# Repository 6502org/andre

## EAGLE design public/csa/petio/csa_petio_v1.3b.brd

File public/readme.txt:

TODO: 

- move unused img sources to ../imgsrc

- make build scripts for sprites, javascript (see below)

create sprite:

- menu items are scaled to 41% to be included in sprite

- cbm/hw/sw/icap icons are not scaled 

minify javascript:

- yui-compressor --nomunge myscripts.js > myscripts-min.js

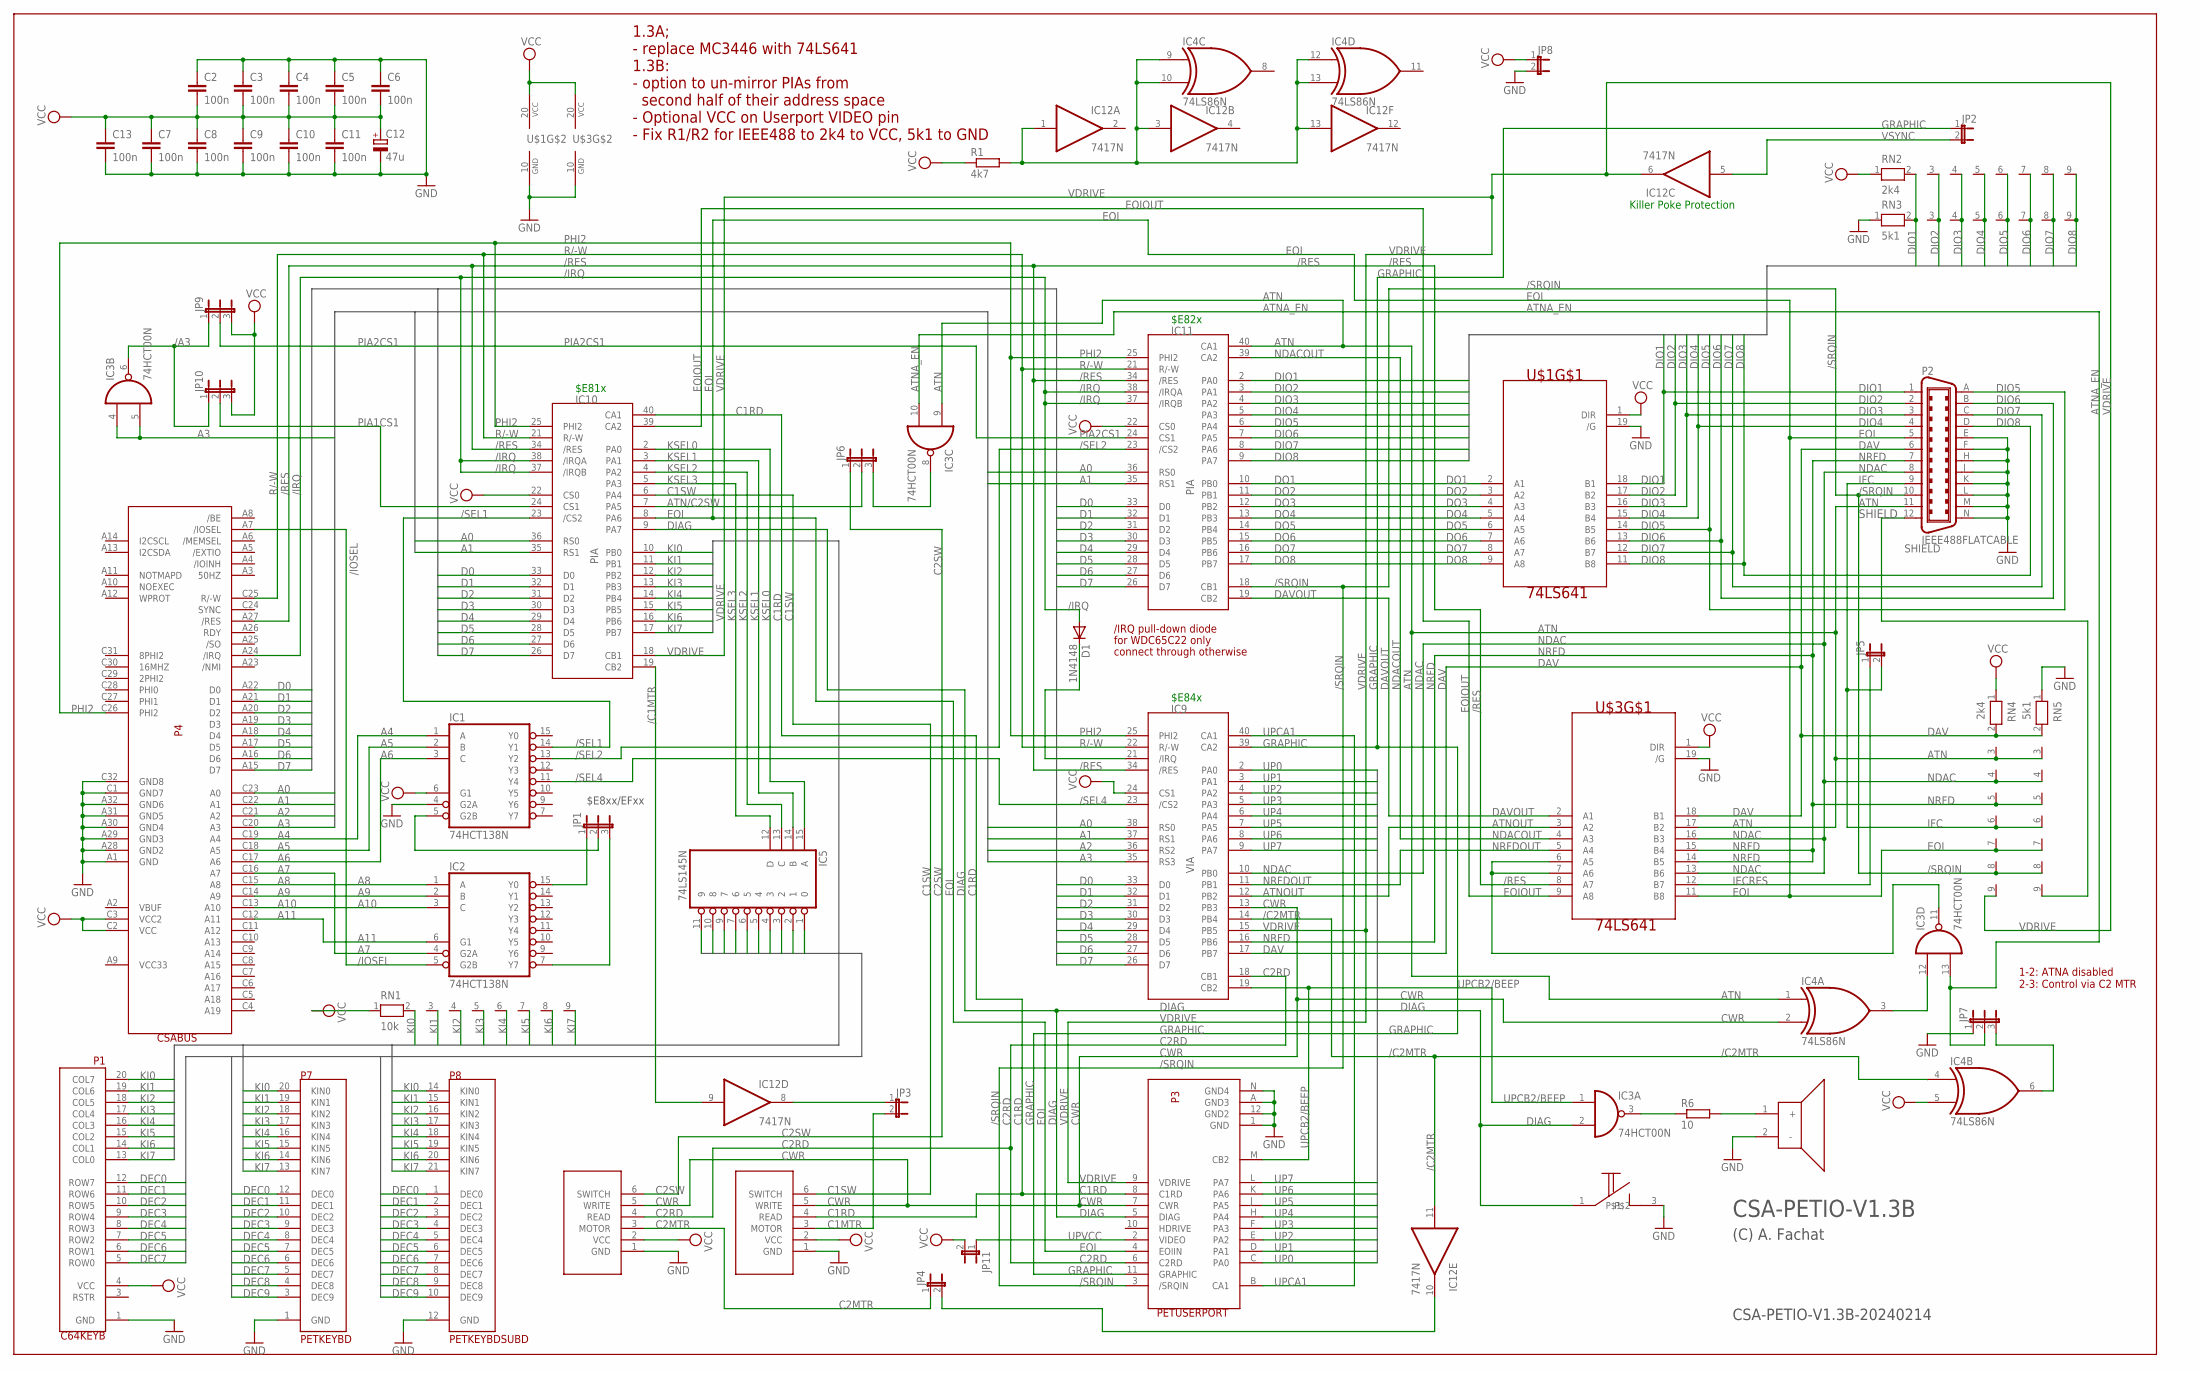
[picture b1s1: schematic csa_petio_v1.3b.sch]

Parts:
BEEP1: PIEZOBEEPERPIEZO; PIEZOBEEPER
C2, C3, C4, C5, C6, C7, C8, C9, C10, C11, C13: 100n; C025-025X050
C12: 47u; E2,5-6
D1: 1N4148; D-5
IC1, IC2: 74HCT138N; DIL16
IC3: 74HCT00N; DIL14
IC4: 74LS86N; DIL14
IC5: 74LS145N; DIL16
IC9: VIA; DIL40
IC10, IC11: PIA; DIL40
IC12: 7417N; DIL14
JP1, JP6, JP7, JP9, JP10: JP2E; JP2
JP2, JP3, JP4, JP5, JP8, JP11: JP1E; JP1
P1: C64KEYB
P2: IEEE488FLATCABLE; FLAT24
P3: PETUSERPORT; FLAT24
P4: CSABUS
P5, P6: CBMTAPE; JP6
P7: PETKEYBD; C64KEYB
P8: PETKEYBDSUBD; SUBD25F
R1: 4k7; 0207/10
R6: 10; 0207/10
RN1: 10k; RN-9
RN2, RN4: 2k4; RN-9
RN3, RN5: 5k1; RN-9
U$1, U$3: 74LS641; DIL20
U$2: TASTER

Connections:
//C2MTR: IC4.6 (O), JP7.3
/A3: IC3.6 (O), JP9.1, JP10.1
/C1MTR: IC10.19 (CB2), IC12.9 (I)
/C2MTR: IC4.4 (I0), IC9.14 (PB4), IC12.11 (I)
/IOSEL: IC2.5 (G2B), P4.A7 (/IOSEL)
/IRQ: D1.A, IC10.37 (/IRQB), IC10.38 (/IRQA), IC11.37 (/IRQB), IC11.38 (/IRQA), P4.A24 (/IRQ)
/RES: IC9.34 (/RES), IC10.34 (/RES), IC11.34 (/RES), P4.A27 (/RES), U$3.8 (A7)
/SEL1: IC1.14 (Y1), IC10.23 (/CS2)
/SEL2: IC1.13 (Y2), IC11.23 (/CS2)
/SEL4: IC1.11 (Y4), IC9.23 (/CS2)
/SRQIN: IC11.18 (CB1), P2.10, P3.3 (/SRQIN), RN4.8, RN5.8
A0: IC9.38 (RS0), IC10.36 (RS0), IC11.36 (RS0), P4.C23 (A0)
A1: IC9.37 (RS1), IC10.35 (RS1), IC11.35 (RS1), P4.C22 (A1)
A2: IC9.36 (RS2), P4.C21 (A2)
A3: IC3.4 (I0), IC3.5 (I1), IC9.35 (RS3), P4.C20 (A3)
A4: IC1.1 (A), P4.C19 (A4)
A5: IC1.2 (B), P4.C18 (A5)
A6: IC1.3 (C), P4.C17 (A6)
A7: IC2.4 (G2A), P4.C16 (A7)
A8: IC2.1 (A), P4.C15 (A8)
A9: IC2.2 (B), P4.C14 (A9)
A10: IC2.3 (C), P4.C13 (A10)
A11: IC2.6 (G1), P4.C12 (A11)
ATN: IC3.9 (I0), IC4.1 (I0), IC11.40 (CA1), P2.11, RN4.3, RN5.3, U$3.17 (B2)
ATN/C2SW: IC10.7 (PA5), JP6.2
ATNA_EN: IC3.10 (I1), IC3.13 (I1), JP7.2
ATNOUT: IC9.12 (PB2), U$3.3 (A2)
C1MTR: JP3.2, P5.3 (MOTOR)
C1RD: IC10.40 (CA1), P3.8 (C1RD), P5.4 (READ)
C1SW: IC10.6 (PA4), P5.6 (SWITCH)
C2MTR: JP4.1, P6.3 (MOTOR)
C2RD: IC9.18 (CB1), P3.6 (C2RD), P6.4 (READ)
C2SW: JP6.1, P6.6 (SWITCH)
CWR: IC4.2 (I1), IC9.13 (PB3), P3.7 (CWR), P5.5 (WRITE), P6.5 (WRITE)
D0: IC9.33 (D0), IC10.33 (D0), IC11.33 (D0), P4.A22 (D0)
D1: IC9.32 (D1), IC10.32 (D1), IC11.32 (D1), P4.A21 (D1)
D2: IC9.31 (D2), IC10.31 (D2), IC11.31 (D2), P4.A20 (D2)
D3: IC9.30 (D3), IC10.30 (D3), IC11.30 (D3), P4.A19 (D3)
D4: IC9.29 (D4), IC10.29 (D4), IC11.29 (D4), P4.A18 (D4)
D5: IC9.28 (D5), IC10.28 (D5), IC11.28 (D5), P4.A17 (D5)
D6: IC9.27 (D6), IC10.27 (D6), IC11.27 (D6), P4.A16 (D6)
D7: IC9.26 (D7), IC10.26 (D7), IC11.26 (D7), P4.A15 (D7)
DAV: IC9.17 (PB7), P2.6, RN4.2, RN5.2, U$3.18 (B1)
DAVOUT: IC11.19 (CB2), U$3.2 (A1)
DEC0: IC5.1 (0), P1.12 (ROW7), P7.12 (DEC0), P8.1 (DEC0)
DEC1: IC5.2 (1), P1.11 (ROW6), P7.11 (DEC1), P8.2 (DEC1)
DEC2: IC5.3 (2), P1.10 (ROW5), P7.10 (DEC2), P8.3 (DEC2)
DEC3: IC5.4 (3), P1.9 (ROW4), P7.9 (DEC3), P8.4 (DEC3)
DEC4: IC5.5 (4), P1.8 (ROW3), P7.8 (DEC4), P8.5 (DEC4)
DEC5: IC5.6 (5), P1.7 (ROW2), P7.7 (DEC5), P8.6 (DEC5)
DEC6: IC5.7 (6), P1.6 (ROW1), P7.6 (DEC6), P8.7 (DEC6)
DEC7: IC5.9 (7), P1.5 (ROW0), P7.5 (DEC7), P8.8 (DEC7)
DEC8: IC5.10 (8), P7.4 (DEC8), P8.9 (DEC8)
DEC9: IC5.11 (9), P7.3 (DEC9), P8.10 (DEC9)
DIAG: IC3.2 (I1), IC10.9 (PA7), P3.5 (DIAG), U$2.1
DIO1: IC11.2 (PA0), P2.1, RN2.2, RN3.2, U$1.18 (B1)
DIO2: IC11.3 (PA1), P2.2, RN2.3, RN3.3, U$1.17 (B2)
DIO3: IC11.4 (PA2), P2.3, RN2.4, RN3.4, U$1.16 (B3)
DIO4: IC11.5 (PA3), P2.4, RN2.5, RN3.5, U$1.15 (B4)
DIO5: IC11.6 (PA4), P2.A (13), RN2.6, RN3.6, U$1.14 (B5)
DIO6: IC11.7 (PA5), P2.B (14), RN2.7, RN3.7, U$1.13 (B6)
DIO7: IC11.8 (PA6), P2.C (15), RN2.8, RN3.8, U$1.12 (B7)
DIO8: IC11.9 (PA7), P2.D (16), RN2.9, RN3.9, U$1.11 (B8)
DO1: IC11.10 (PB0), U$1.2 (A1)
DO2: IC11.11 (PB1), U$1.3 (A2)
DO3: IC11.12 (PB2), U$1.4 (A3)
DO4: IC11.13 (PB3), U$1.5 (A4)
DO5: IC11.14 (PB4), U$1.6 (A5)
DO6: IC11.15 (PB5), U$1.7 (A6)
DO7: IC11.16 (PB6), U$1.8 (A7)
DO8: IC11.17 (PB7), U$1.9 (A8)
EOI: IC10.8 (PA6), P2.5, P3.4 (EOIIN), RN4.7, RN5.7, U$3.11 (B8)
EOIOUT: IC10.39 (CA2), U$3.9 (A8)
GND: BEEP1.2 (-), C2.1, C3.1, C4.1, C5.1, C6.1, C7.2, C8.2, C9.2, C10.2, C11.2, C12.-, C13.2, IC1.4 (G2A), IC1.8 (GND), IC2.8 (GND), IC3.7 (GND), IC4.7 (GND), IC5.8 (GND), IC9.1 (GND), IC10.1 (GND), IC11.1 (GND), IC12.7 (GND), JP7.1, JP8.2, P1.1 (GND), P2.E (17), P2.F (18), P2.H (19), P2.J (20), P2.K (21), P2.L (22), P2.M (23), P2.N (24), P3.1 (GND), P3.12 (GND2), P3.A (GND3), P3.N (GND4), P4.A1 (GND), P4.A28 (GND2), P4.A29 (GND3), P4.A30 (GND4), P4.A31 (GND5), P4.A32 (GND6), P4.C1 (GND7), P4.C32 (GND8), P5.1 (GND), P6.1 (GND), P7.1 (GND), P8.12 (GND), RN3.1, RN5.1, U$1.10 (GND), U$1.19 (/G), U$2.3, U$3.10 (GND), U$3.19 (/G)
GRAPHIC: IC9.39 (CA2), JP2.1, P3.11 (GRAPHIC)
IECRES: JP5.1, U$3.12 (B7)
IFC: JP5.2, P2.9, RN4.6, RN5.6
KI0: IC10.10 (PB0), P1.20 (COL7), P7.20 (KIN0), P8.14 (KIN0), RN1.2
KI1: IC10.11 (PB1), P1.19 (COL6), P7.19 (KIN1), P8.15 (KIN1), RN1.3
KI2: IC10.12 (PB2), P1.18 (COL5), P7.18 (KIN2), P8.16 (KIN2), RN1.4
KI3: IC10.13 (PB3), P1.17 (COL4), P7.17 (KIN3), P8.17 (KIN3), RN1.5
KI4: IC10.14 (PB4), P1.16 (COL3), P7.16 (KIN4), P8.18 (KIN4), RN1.6
KI5: IC10.15 (PB5), P1.15 (COL2), P7.15 (KIN5), P8.19 (KIN5), RN1.7
KI6: IC10.16 (PB6), P1.14 (COL1), P7.14 (KIN6), P8.20 (KIN6), RN1.8
KI7: IC10.17 (PB7), P1.13 (COL0), P7.13 (KIN7), P8.21 (KIN7), RN1.9
KSEL0: IC5.15 (A), IC10.2 (PA0)
KSEL1: IC5.14 (B), IC10.3 (PA1)
KSEL2: IC5.13 (C), IC10.4 (PA2)
KSEL3: IC5.12 (D), IC10.5 (PA3)
unnamed: IC3.12 (I0), IC4.3 (O)
unnamed: IC3.11 (O), U$3.6 (A5), U$3.7 (A6)
unnamed: IC3.3 (O), R6.1
unnamed: BEEP1.1 (+), R6.2
unnamed: D1.C, IC9.21 (/IRQ)
unnamed: IC3.8 (O), JP6.3
unnamed: IC12.8 (O), JP3.1
unnamed: IC12.10 (O), JP4.2
unnamed: IC1.5 (G2B), JP1.2
unnamed: IC2.15 (Y0), JP1.1
unnamed: IC2.7 (Y7), JP1.3
NDAC: IC9.10 (PB0), P2.8, RN4.4, RN5.4, U$3.13 (B6), U$3.16 (B3)
NDACOUT: IC11.39 (CA2), U$3.4 (A3)
NRFD: IC9.16 (PB6), P2.7, RN4.5, RN5.5, U$3.14 (B5), U$3.15 (B4)
NRFDOUT: IC9.11 (PB1), U$3.5 (A4)
OPENHIGH: IC4.9 (I0), IC4.10 (I1), IC4.12 (I0), IC4.13 (I1), IC12.1 (I), IC12.3 (I), IC12.13 (I), R1.2
PHI2: IC9.25 (PHI2), IC10.25 (PHI2), IC11.25 (PHI2), P4.C26 (PHI2)
PIA1CS1: IC10.24 (CS1), JP10.2
PIA2CS1: IC11.24 (CS1), JP9.2
R/-W: IC9.22 (R/-W), IC10.21 (R/-W), IC11.21 (R/-W), P4.C25 (R/-W)
SHIELD: P2.12, RN5.9
UP0: IC9.2 (PA0), P3.C (PA0)
UP1: IC9.3 (PA1), P3.D (PA1)
UP2: IC9.4 (PA2), P3.E (PA2)
UP3: IC9.5 (PA3), P3.F (PA3)
UP4: IC9.6 (PA4), P3.H (PA4)
UP5: IC9.7 (PA5), P3.J (PA5)
UP6: IC9.8 (PA6), P3.K (PA6)
UP7: IC9.9 (PA7), P3.L (PA7)
UPCA1: IC9.40 (CA1), P3.B (CA1)
UPCB2/BEEP: IC3.1 (I0), IC9.19 (CB2), P3.M (CB2)
UPVCC: JP11.1, P3.2 (VIDEO)
VCC: C2.2, C3.2, C4.2, C5.2, C6.2, C7.1, C8.1, C9.1, C10.1, C11.1, C12.+, C13.1, IC1.6 (G1), IC1.16 (VCC), IC2.16 (VCC), IC3.14 (VCC), IC4.5 (I1), IC4.14 (VCC), IC5.16 (VCC), IC9.20 (VCC), IC9.24 (CS1), IC10.20 (VCC), IC10.22 (CS0), IC11.20 (VCC), IC11.22 (CS0), IC12.14 (VCC), JP8.1, JP9.3, JP10.3, JP11.2, P1.4 (VCC), P4.C2 (VCC), P4.C3 (VCC2), P5.2 (VCC), P6.2 (VCC), R1.1, RN1.1, RN2.1, RN4.1, U$1.1 (DIR), U$1.20 (VCC), U$3.1 (DIR), U$3.20 (VCC)
VDRIVE: IC9.15 (PB5), IC10.18 (CB1), IC12.6 (O), P3.9 (VDRIVE), RN4.9
VSYNC: IC12.5 (I), JP2.2

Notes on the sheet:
$E8xx/EFxx
CSA-PETIO-V1.3B-20240214
CSA-PETIO-V1.3B
(C) A. Fachat
Killer Poke Protection
$E82x
$E84x
$E81x
/IRQ pull-down diode
for WDC65C22 only
connect through otherwise
1.3A; - replace MC3446 with 74LS641 1.3B: - option to un-mirror PIAs from second half of their address space - Optional VCC on Userport VIDEO pin - Fix R1/R2 for IEEE488 to 2k4 to VCC, 5k1 to GND
1-2: ATNA disabled 2-3: Control via C2 MTR

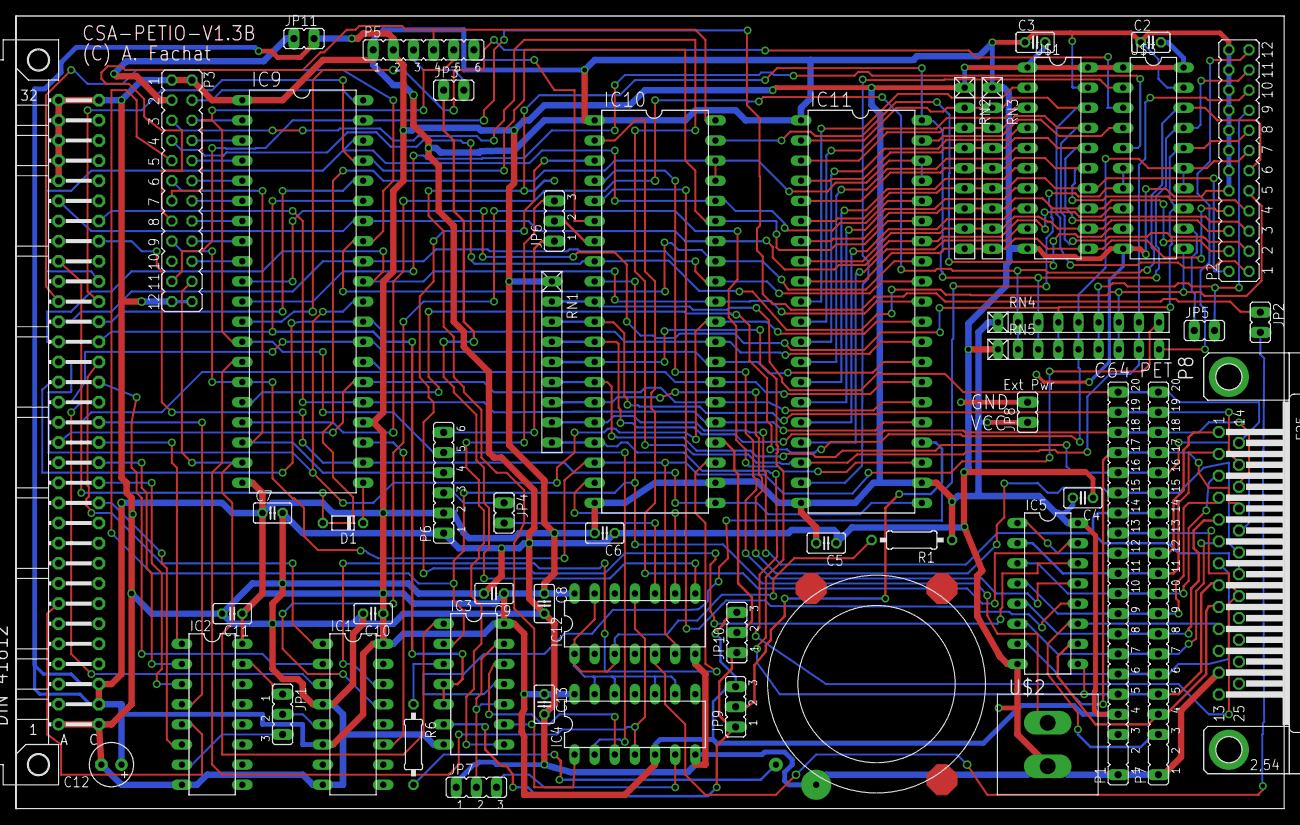
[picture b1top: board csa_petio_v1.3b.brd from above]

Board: 2 copper layers, 160.0 x 100.0 mm, 52 parts (0 on the bottom side), 124 nets.

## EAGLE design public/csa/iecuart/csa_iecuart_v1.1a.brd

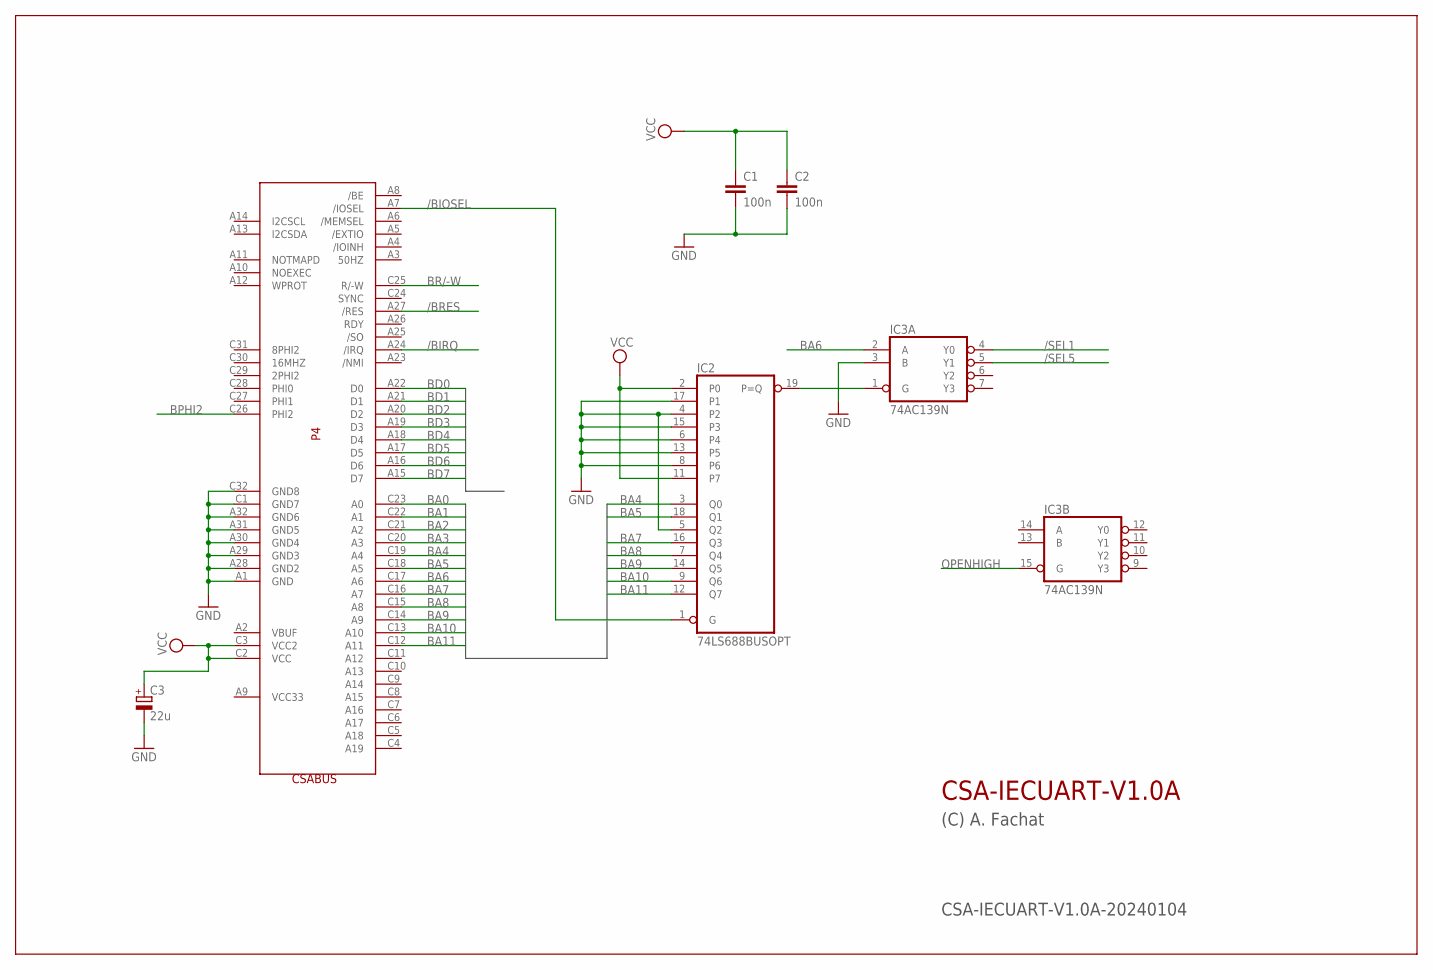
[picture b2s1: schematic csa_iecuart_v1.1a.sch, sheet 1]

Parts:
C1, C2: 100n; C025-024X044
C3: 22u; E2,5-7
IC2: 74LS688BUSOPT; DIL20
IC3: 74AC139N; DIL16
P4: CSABUS

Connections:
/BIOSEL: IC2.1 (G), P4.A7 (/IOSEL)
/BIRQ: P4.A24 (/IRQ); also elsewhere on the board
/BRES: P4.A27 (/RES); also elsewhere on the board
/SEL1: IC3.4 (Y0); also elsewhere on the board
/SEL5: IC3.5 (Y1); also elsewhere on the board
BA0: P4.C23 (A0); also elsewhere on the board
BA1: P4.C22 (A1); also elsewhere on the board
BA2: P4.C21 (A2); also elsewhere on the board
BA3: P4.C20 (A3); also elsewhere on the board
BA4: IC2.3 (Q0), P4.C19 (A4)
BA5: IC2.18 (Q1), P4.C18 (A5)
BA6: IC3.2 (A), P4.C17 (A6)
BA7: IC2.16 (Q3), P4.C16 (A7)
BA8: IC2.7 (Q4), P4.C15 (A8)
BA9: IC2.14 (Q5), P4.C14 (A9)
BA10: IC2.9 (Q6), P4.C13 (A10)
BA11: IC2.12 (Q7), P4.C12 (A11)
BD0: P4.A22 (D0); also elsewhere on the board
BD1: P4.A21 (D1); also elsewhere on the board
BD2: P4.A20 (D2); also elsewhere on the board
BD3: P4.A19 (D3); also elsewhere on the board
BD4: P4.A18 (D4); also elsewhere on the board
BD5: P4.A17 (D5); also elsewhere on the board
BD6: P4.A16 (D6); also elsewhere on the board
BD7: P4.A15 (D7); also elsewhere on the board
BPHI2: P4.C26 (PHI2); also elsewhere on the board
BR/-W: P4.C25 (R/-W); also elsewhere on the board
GND: C1.2, C2.2, C3.-, IC2.4 (P2), IC2.5 (Q2), IC2.6 (P4), IC2.8 (P6), IC2.10 (GND), IC2.13 (P5), IC2.15 (P3), IC2.17 (P1), IC3.3 (B), IC3.8 (GND), P4.A1 (GND), P4.A28 (GND2), P4.A29 (GND3), P4.A30 (GND4), P4.A31 (GND5), P4.A32 (GND6), P4.C1 (GND7), P4.C32 (GND8); also elsewhere on the board
unnamed: IC2.19 (P=Q), IC3.1 (G)
OPENHIGH: IC3.15 (G); also elsewhere on the board
VCC: C1.1, C2.1, C3.+, IC2.2 (P0), IC2.11 (P7), IC2.20 (VCC), IC3.16 (VCC), P4.C2 (VCC), P4.C3 (VCC2); also elsewhere on the board

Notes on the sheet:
CSA-IECUART-V1.0A-20240104
(C) A. Fachat
CSA-IECUART-V1.0A

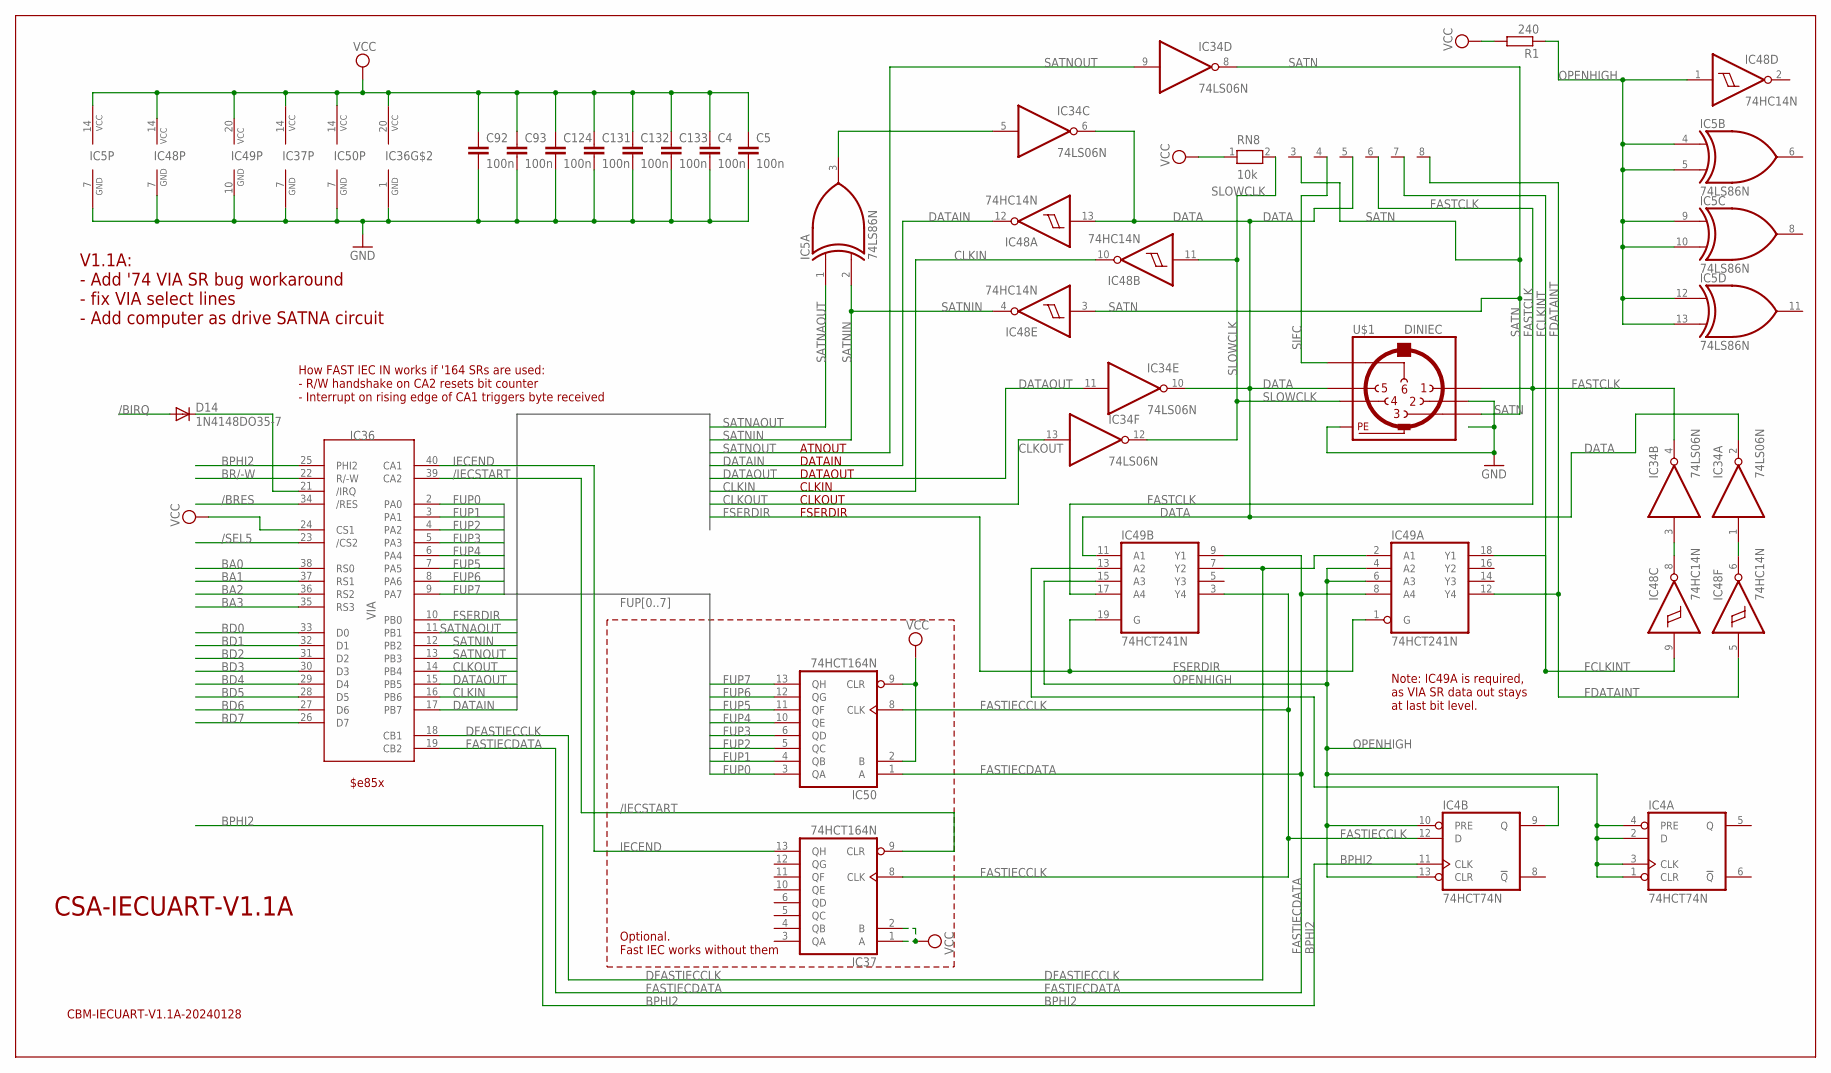
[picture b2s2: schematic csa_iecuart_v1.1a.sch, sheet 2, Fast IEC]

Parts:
C4, C5, C92, C93, C124, C131, C132, C133: 100n; C025-024X044
D14: 1N4148DO35-7; DO35-7
IC4: 74HCT74N; DIL14
IC5: 74LS86N; DIL14
IC34: 74LS06N; DIL14
IC36: VIA; DIL40
IC37, IC50: 74HCT164N; DIL14
IC48: 74HC14N; DIL14
IC49: 74HCT241N; DIL20
R1: 240; 0207/10
RN8: 10k; RN-8
U$1: DINIEC; DIN6PIEC

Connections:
/BIRQ: D14.A; also elsewhere on the board
/BRES: IC36.34 (/RES); also elsewhere on the board
/IECSTART: IC36.39 (CA2), IC37.9 (CLR)
/SEL5: IC36.23 (/CS2); also elsewhere on the board
BA0: IC36.38 (RS0); also elsewhere on the board
BA1: IC36.37 (RS1); also elsewhere on the board
BA2: IC36.36 (RS2); also elsewhere on the board
BA3: IC36.35 (RS3); also elsewhere on the board
BD0: IC36.33 (D0); also elsewhere on the board
BD1: IC36.32 (D1); also elsewhere on the board
BD2: IC36.31 (D2); also elsewhere on the board
BD3: IC36.30 (D3); also elsewhere on the board
BD4: IC36.29 (D4); also elsewhere on the board
BD5: IC36.28 (D5); also elsewhere on the board
BD6: IC36.27 (D6); also elsewhere on the board
BD7: IC36.26 (D7); also elsewhere on the board
BPHI2: IC4.11 (CLK), IC36.25 (PHI2); also elsewhere on the board
BR/-W: IC36.22 (R/-W); also elsewhere on the board
CLKIN: IC36.16 (PB6), IC48.10 (O)
CLKOUT: IC34.13 (I), IC36.14 (PB4)
DATA: IC34.2 (O), IC34.6 (O), IC34.10 (O), IC48.13 (I), IC49.11 (A1), RN8.5, U$1.5
DATAIN: IC36.17 (PB7), IC48.12 (O)
DATAOUT: IC34.11 (I), IC36.15 (PB5)
DFASTIECCLK: IC36.18 (CB1), IC49.2 (A1), IC49.7 (Y2)
FASTCLK: IC34.4 (O), IC49.17 (A4), RN8.6, U$1.1
FASTIECCLK: IC4.12 (D), IC37.8 (CLK), IC49.3 (Y4), IC50.8 (CLK)
FASTIECDATA: IC36.19 (CB2), IC49.8 (A4), IC49.9 (Y1), IC50.1 (A)
FCLKINT: IC48.9 (I), IC49.18 (Y1), RN8.7
FDATAINT: IC48.5 (I), IC49.12 (Y4), RN8.8
FSERDIR: IC36.10 (PB0), IC49.1 (G), IC49.19 (G)
FUP0: IC36.2 (PA0), IC50.3 (QA)
FUP1: IC36.3 (PA1), IC50.4 (QB)
FUP2: IC36.4 (PA2), IC50.5 (QC)
FUP3: IC36.5 (PA3), IC50.6 (QD)
FUP4: IC36.6 (PA4), IC50.10 (QE)
FUP5: IC36.7 (PA5), IC50.11 (QF)
FUP6: IC36.8 (PA6), IC50.12 (QG)
FUP7: IC36.9 (PA7), IC50.13 (QH)
GND: C4.2, C5.2, C92.2, C93.2, C124.2, C131.2, C132.2, C133.2, IC4.7 (GND), IC5.7 (GND), IC34.7 (GND), IC36.1 (GND), IC37.7 (GND), IC48.7 (GND), IC49.10 (GND), IC50.7 (GND), U$1.2, U$1.PE, U$1.PE@ (PE), U$1.PE@1 (PE), U$1.PE@2 (PE); also elsewhere on the board
IECEND: IC36.40 (CA1), IC37.13 (QH)
unnamed: IC34.1 (I), IC48.6 (O)
unnamed: IC34.3 (I), IC48.8 (O)
unnamed: IC4.9 (Q), IC49.13 (A2)
unnamed: IC5.3 (O), IC34.5 (I)
unnamed: D14.C, IC36.21 (/IRQ)
OPENHIGH: IC4.1 (CLR), IC4.2 (D), IC4.3 (CLK), IC4.4 (PRE), IC4.10 (PRE), IC4.13 (CLR), IC5.4 (I0), IC5.5 (I1), IC5.9 (I0), IC5.10 (I1), IC5.12 (I0), IC5.13 (I1), IC48.1 (I), IC49.4 (A2), IC49.6 (A3), IC49.15 (A3), R1.1; also elsewhere on the board
SATN: IC34.8 (O), IC48.3 (I), RN8.3, U$1.3
SATNAOUT: IC5.1 (I0), IC36.11 (PB1)
SATNIN: IC5.2 (I1), IC36.12 (PB2), IC48.4 (O)
SATNOUT: IC34.9 (I), IC36.13 (PB3)
SIFC: RN8.4, U$1.6
SLOWCLK: IC34.12 (O), IC48.11 (I), RN8.2, U$1.4
VCC: C4.1, C5.1, C92.1, C93.1, C124.1, C131.1, C132.1, C133.1, IC4.14 (VCC), IC5.14 (VCC), IC34.14 (VCC), IC36.20 (VCC), IC36.24 (CS1), IC37.1 (A), IC37.2 (B), IC37.14 (VCC), IC48.14 (VCC), IC49.20 (VCC), IC50.2 (B), IC50.9 (CLR), IC50.14 (VCC), R1.2, RN8.1; also elsewhere on the board

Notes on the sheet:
CLKIN
CLKOUT
DATAIN
DATAOUT
ATNOUT
FSERDIR
Note: IC49A is required, as VIA SR data out stays at last bit level.
Optional. Fast IEC works without them
How FAST IEC IN works if '164 SRs are used: - R/W handshake on CA2 resets bit counter - Interrupt on rising edge of CA1 triggers byte received
$e85x
CSA-IECUART-V1.1A
CBM-IECUART-V1.1A-20240128
V1.1A: - Add '74 VIA SR bug workaround - fix VIA select lines - Add computer as drive SATNA circuit

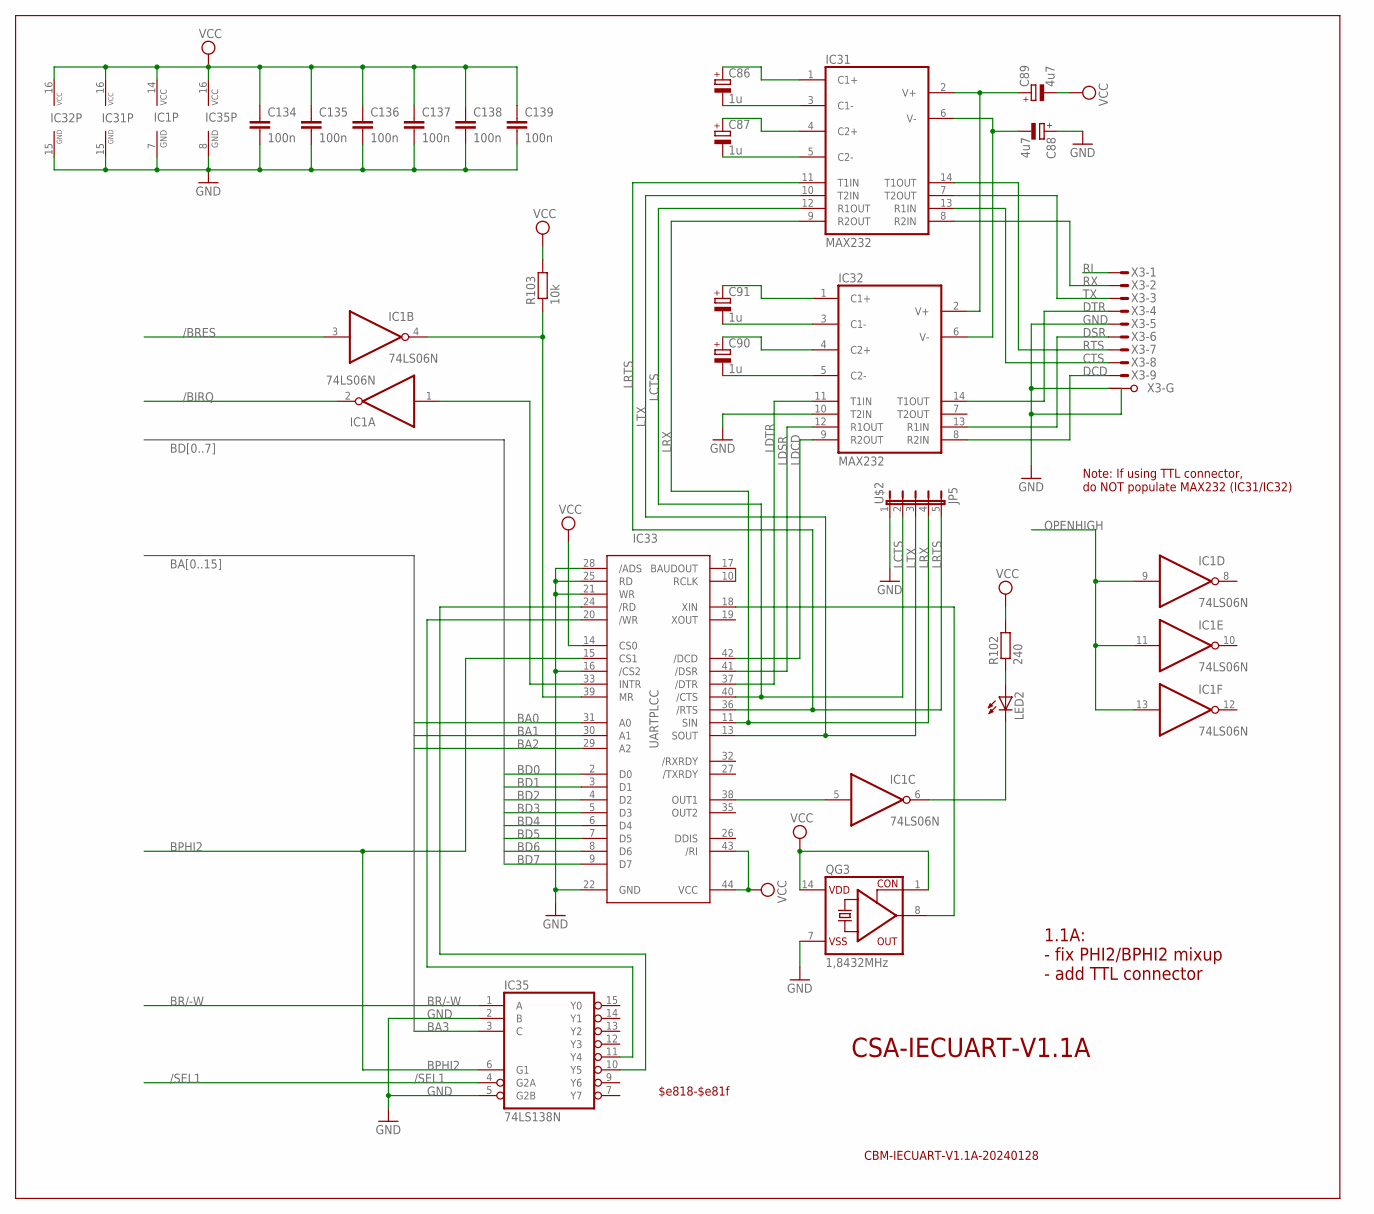
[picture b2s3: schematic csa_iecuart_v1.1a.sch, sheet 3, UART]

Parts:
C86, C87, C90, C91: 1u; E2,5-6
C88, C89: 4u7; E2,5-6
C134, C135, C136, C137, C138, C139: 100n; C025-024X044
IC1: 74LS06N; DIL14
IC31, IC32: MAX232; DIL16
IC33: UARTPLCC; PLCC44
IC35: 74LS138N; DIL16
LED2: LED3MM
QG3: 1,8432MHz; SG51
R102: 240; 0207/10
R103: 10k; 0207/10
U$2: JP5
X3: M09HPS; M09HP

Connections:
/BIRQ: IC1.2 (O); also elsewhere on the board
/BRES: IC1.3 (I); also elsewhere on the board
/SEL1: IC35.4 (G2A); also elsewhere on the board
BA0: IC33.31 (A0); also elsewhere on the board
BA1: IC33.30 (A1); also elsewhere on the board
BA2: IC33.29 (A2); also elsewhere on the board
BA3: IC35.3 (C); also elsewhere on the board
BD0: IC33.2 (D0); also elsewhere on the board
BD1: IC33.3 (D1); also elsewhere on the board
BD2: IC33.4 (D2); also elsewhere on the board
BD3: IC33.5 (D3); also elsewhere on the board
BD4: IC33.6 (D4); also elsewhere on the board
BD5: IC33.7 (D5); also elsewhere on the board
BD6: IC33.8 (D6); also elsewhere on the board
BD7: IC33.9 (D7); also elsewhere on the board
BPHI2: IC33.15 (CS1), IC35.6 (G1); also elsewhere on the board
BR/-W: IC35.1 (A); also elsewhere on the board
CTS: IC31.13 (R1IN), X3.8 (M)
DCD: IC32.8 (R2IN), X3.9 (M)
DSR: IC32.13 (R1IN), X3.6 (M)
DTR: IC32.14 (T1OUT), X3.4 (M)
GND: C88.+, C134.2, C135.2, C136.2, C137.2, C138.2, C139.2, IC1.7 (GND), IC31.15 (GND), IC32.10 (T2IN), IC32.15 (GND), IC33.16 (/CS2), IC33.21 (WR), IC33.22 (GND), IC33.25 (RD), IC33.28 (/ADS), IC35.2 (B), IC35.5 (G2B), IC35.8 (GND), QG3.7 (VSS), U$2.1, X3.5 (M), X3.G1, X3.G2; also elsewhere on the board
LCTS: IC31.12 (R1OUT), IC33.40 (/CTS), U$2.2
LDCD: IC32.9 (R2OUT), IC33.42 (/DCD)
LDSR: IC32.12 (R1OUT), IC33.41 (/DSR)
LDTR: IC32.11 (T1IN), IC33.37 (/DTR)
LRTS: IC31.11 (T1IN), IC33.36 (/RTS), U$2.5
LRX: IC31.9 (R2OUT), IC33.11 (SIN), U$2.4
LTX: IC31.10 (T2IN), IC33.13 (SOUT), U$2.3
unnamed: IC33.18 (XIN), QG3.8 (OUT)
unnamed: C86.-, IC31.3 (C1-)
unnamed: C86.+, IC31.1 (C1+)
unnamed: C91.-, IC32.3 (C1-)
unnamed: C91.+, IC32.1 (C1+)
unnamed: C87.-, IC31.5 (C2-)
unnamed: C87.+, IC31.4 (C2+)
unnamed: C90.-, IC32.5 (C2-)
unnamed: C90.+, IC32.4 (C2+)
unnamed: C88.-, IC31.6 (V-), IC32.6 (V-)
unnamed: C89.+, IC31.2 (V+), IC32.2 (V+)
unnamed: IC33.10 (RCLK), IC33.17 (BAUDOUT)
unnamed: IC1.1 (I), IC33.33 (INTR)
unnamed: IC33.20 (/WR), IC35.11 (Y4)
unnamed: IC33.24 (/RD), IC35.10 (Y5)
unnamed: LED2.A, R102.1
unnamed: IC1.5 (I), IC33.38 (OUT1)
unnamed: IC1.6 (O), LED2.K (C)
OPENHIGH: IC1.9 (I), IC1.11 (I), IC1.13 (I); also elsewhere on the board
RI: X3.1 (M)
RTS: IC31.14 (T1OUT), X3.7 (M)
RX: IC31.8 (R2IN), X3.2 (M)
TX: IC31.7 (T2OUT), X3.3 (M)
UARTRES: IC1.4 (O), IC33.39 (MR), R103.1
VCC: C89.-, C134.1, C135.1, C136.1, C137.1, C138.1, C139.1, IC1.14 (VCC), IC31.16 (VCC), IC32.16 (VCC), IC33.14 (CS0), IC33.43 (/RI), IC33.44 (VCC), IC35.16 (VCC), QG3.1 (CON), QG3.14 (VDD), R102.2, R103.2; also elsewhere on the board

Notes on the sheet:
$e818-$e81f
CSA-IECUART-V1.1A
CBM-IECUART-V1.1A-20240128
1.1A: - fix PHI2/BPHI2 mixup - add TTL connector
Note: If using TTL connector, do NOT populate MAX232 (IC31/IC32)

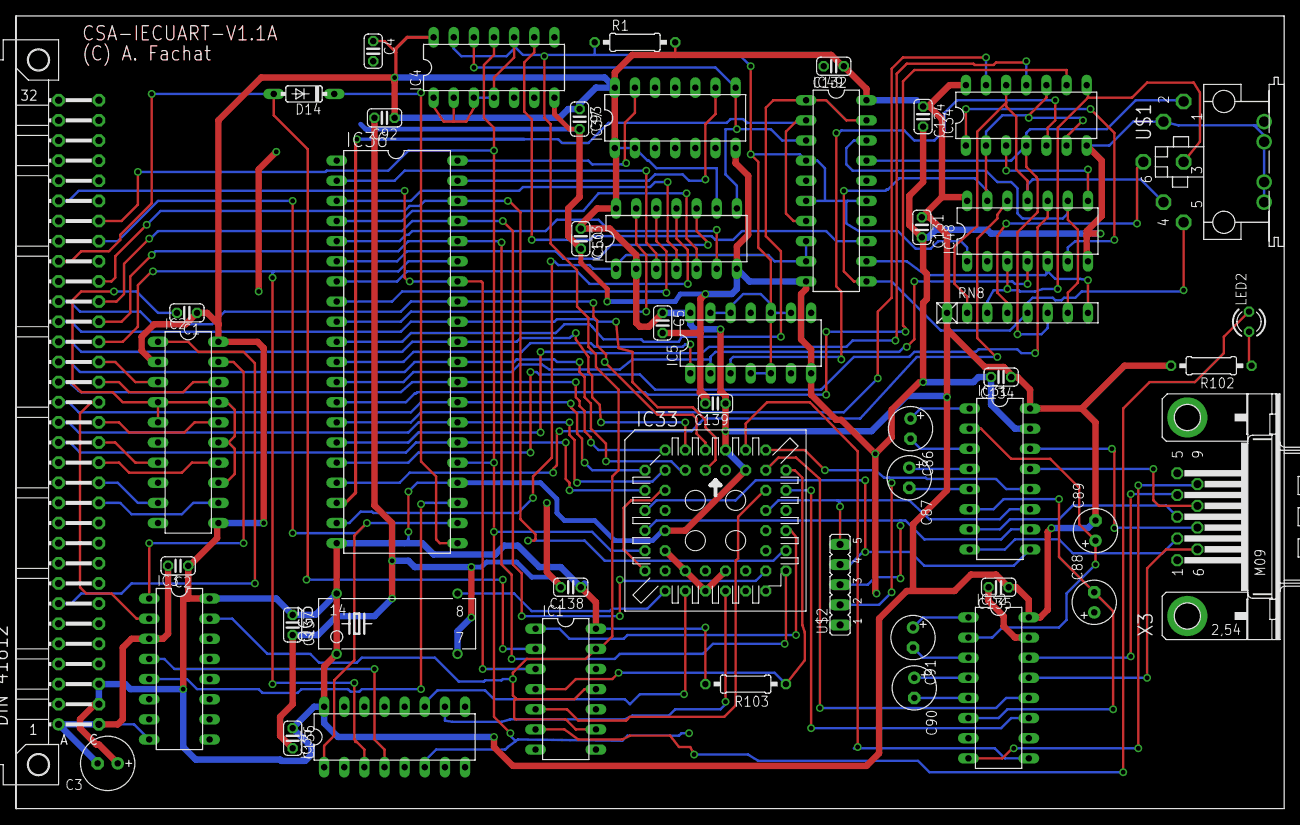
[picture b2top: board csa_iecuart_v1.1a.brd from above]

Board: 2 copper layers, 160.0 x 100.0 mm, 49 parts (0 on the bottom side), 97 nets.
